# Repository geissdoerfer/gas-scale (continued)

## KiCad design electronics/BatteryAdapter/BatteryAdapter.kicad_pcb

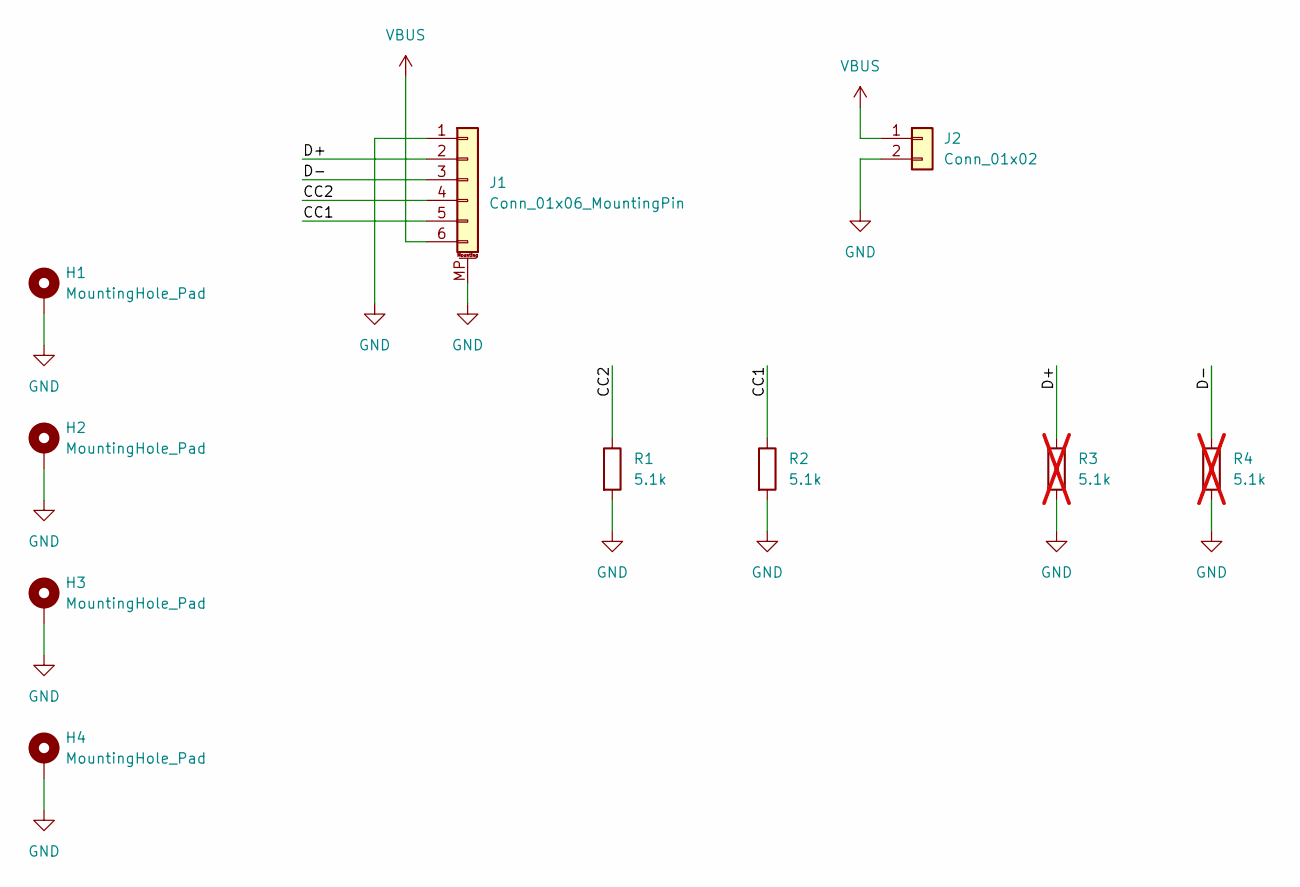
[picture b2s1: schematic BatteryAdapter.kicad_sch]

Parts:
H1, H2, H3, H4: MountingHole_Pad; MountingHole_3.2mm_M3_Pad_TopBottom
J1: Conn_01x06_MountingPin; JST_PH_S6B-PH-SM4-TB_1x06-1MP_P2.00mm_Horizontal
J2: Conn_01x02; SolderPads
R1, R2: 5.1k; R_0603_1608Metric
R3, R4: 5.1k; R_0603_1608Metric; not fitted

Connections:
/CC1: J1.5, R2.1
/CC2: J1.4, R1.1
/D+: J1.2, R3.1
/D-: J1.3, R4.1
GND: H1.1 (1_1), H2.1 (1_1), H3.1 (1_1), H4.1 (1_1), J1.1, J1.MP (MountPin), J2.2, R1.2, R2.2, R3.2, R4.2
VBUS: J1.6, J2.1

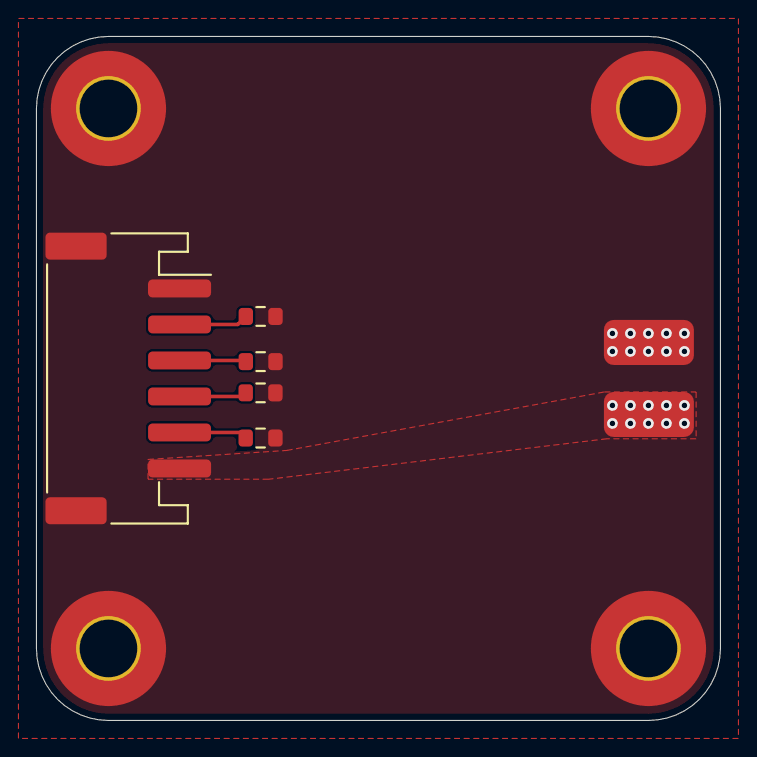
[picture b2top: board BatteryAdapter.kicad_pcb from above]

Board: 2 copper layers, 38.0 x 38.0 mm, 10 parts (0 on the bottom side), 6 nets.

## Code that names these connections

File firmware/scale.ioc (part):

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Mcu.Name=STM32U083CCUx
Mcu.Package=UFQFPN48
Mcu.UserName=STM32U083CCUx
PA0.Signal=SharedAnalog_PA0
PA10.Mode=Asynchronous
PA10.Signal=USART1_RX
PA2.GPIOParameters=GPIO_Label
PA2.GPIO_Label=RadioPwrKey
PA2.Signal=GPIO_Output
PA3.GPIOParameters=GPIO_Label
PA3.GPIO_Label=Led
PA3.Signal=GPIO_Output
PA5.Mode=Asynchronous
PA5.Signal=USART3_TX
PA6.GPIOParameters=GPIO_Label
PA6.GPIO_Label=CellsEnable
PA6.Signal=GPIO_Output
PA7.Mode=Asynchronous
PA7.Signal=USART3_RX
PA9.Mode=Asynchronous
PA9.Signal=USART1_TX
PB1.Signal=GPXTI1
PB12.GPIOParameters=GPIO_Label
PB12.GPIO_Label=Sck
PB12.Signal=GPIO_Output
PB13.GPIOParameters=GPIO_Label
PB13.GPIO_Label=Dout
PB13.Signal=GPIO_Input
PB4.GPIOParameters=GPIO_Label
PB4.GPIO_Label=RadioEnable
PB4.Signal=GPIO_Output
PB9.GPIOParameters=GPIO_Label
PB9.GPIO_Label=BatSenseEnable
PB9.Signal=GPIO_Output
PC14-OSC32_IN.Mode=LSE-External-Oscillator
PC14-OSC32_IN.Signal=RCC_OSC32_IN
PC15-OSC32_OUT.Mode=LSE-External-Oscillator
PC15-OSC32_OUT.Signal=RCC_OSC32_OUT
RCC.HSE_VALUE=4000000
RCC.SYSCLKFreq_VALUE=16000000
board=custom

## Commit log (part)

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2026-01-23 bugfix and tests
2026-01-23 add mosquitto broker
2026-01-23 add frontend
2026-01-29 add firmware
2026-01-30 load -> weight
2026-01-30 firmware: send json to correct topic
2026-01-30 add housing design files
2026-02-23 move to post-factum calibration
2026-02-24 implement dynamic plots in webinterface
2026-03-11 add electronics
2026-03-11 frontend: add bar chart with consumption
2026-03-19 sync
2026-03-19 finalize clamps on housing
2026-03-31 housing: add cylinder step model
2026-04-02 housing: add new big model
2026-04-02 work on big version
2026-04-08 work on housing
2026-04-09 housing: add good feet
2026-04-12 housing: add holes to ring and hood
2026-04-12 housing: finalize thread insert holes etc
2026-04-12 electronics: start with A7670 module
2026-04-13 housing: add flat spot for USB
2026-04-13 housing: add cutoout for USB connector
2026-04-14 schematics
2026-04-14 housing: minor updates
2026-04-15 firmware: add stm32 ioc file
2026-04-15 electronics: replace charger
2026-04-15 electronics: select footprints
2026-04-16 electronics: initial placement
2026-04-16 electronics: start routing
2026-04-17 electronics: more routing
2026-04-17 electronics: sync
2026-04-19 electronics: replace A7670 footprint
2026-04-20 electronics: add 3D model of A7670 module
2026-04-20 electronics: add 3D models
2026-04-21 electronics: final touches
2026-04-21 electronics: add cutout for USB-C connector
2026-04-21 electronics: add MPNs
2026-04-21 housing: add PCB mounting holes
2026-04-22 housing: add battery holder
2026-04-27 housing: increase ring thickness
2026-04-28 housing: increase hole size on ring
2026-05-04 housing: increase housing to 420mm dia
2026-05-05 firmware: add led blink
2026-05-06 firmware: hello world working
2026-05-06 firmware: uart bridge to lte module
2026-05-06 firmware: working internet connection
2026-05-07 electronics: simplify BOM and fix issues
2026-05-10 firmware: mqtt publish working
2026-05-10 firmware: hologram internet and hx711 driver working
2026-05-10 firmware: publish actual load cell reading
2026-05-13 housing: fillet ring
2026-05-15 electronics: improve deistribution
2026-05-15 electronics: add 2x2 panelization
2026-05-16 electronics: fix panelization for JLC
2026-05-25 firmware: change topic and interval
2026-05-25 server: ssl encrpyted connection to hivemq
2026-05-25 housing: add gitignore
2026-05-25 electronics: update
2026-05-29 use low power sleep between publish events
2026-05-29 firmware: enable RTC
2026-05-29 firmware: enable low power sleep
2026-05-29 firmware: gitignore generated RTC config files
2026-06-02 firmware: add battery voltage sensing
2026-06-02 firmware: move adc sampling to own function
2026-06-02 firmware: move to firmware directory
2026-06-03 firmware: restart Module on MQTT error
2026-06-03 firmware: publish counter of module restarts
2026-06-03 electronics: remove testpoints from BOM
2026-06-03 mqtt-ingestor: adjust to shortened json string
2026-06-04 housing: move PCB to match cable lengths
2026-06-04 housing: make stand threads self tapping
2026-06-04 housing: add documentation of screws
2026-06-04 add BOM
2026-06-08 housing: add cube for cutting connector part
2026-06-24 housing: work on screws
2026-06-24 backend: allow remote access
2026-06-24 update bom
2026-06-24 electronics: add values for charger
2026-06-25 housing: add location for charging adapter board
2026-06-28 electronics: add battery adapter PCB
